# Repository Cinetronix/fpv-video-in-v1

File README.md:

# Cinetronix FPV Video Input Board v1

KiCad hardware design for an HDMI-to-MIPI CSI bridge board, designed for FPV camera systems.

## Overview

Converts HDMI video input to MIPI CSI-2 output using the Toshiba TC9590XBG bridge IC, controlled by an ESP32-S3 microcontroller.

### Key Components

| Component | Function |
|-----------|----------|
| TC9590XBG | HDMI to MIPI CSI-2 bridge |
| ESP32-S3 | Control MCU |
| TS5MP645YFPR | HDMI multiplexer |
| TPD8S009DSMR | HDMI ESD protection |
| TPD6E05U06RVZR | Additional ESD protection |
| DF56C-26S | Micro-coax connector (CSI output) |

## Board Designs

- **TC9590XBG-PCB/** — Main board with HDMI input, CSI output, and ESP32-S3 control
- **DF56C-26S-breakout-board-PCB/** — Breakout board for the 26-pin DF56C micro-coax connector
- **DF56C-30S-breakout-board-PCB/** — Breakout board for the 30-pin DF56C micro-coax connector

## Requirements

- [KiCad](https://www.kicad.org/) 7+
- [KiKit](https://github.com/yaqwsx/KiKit) (for panel generation)

## Panelization

Generate a manufacturing panel from the `TC9590XBG-PCB/` directory:

```bash
kikit panelize \
    --layout "grid; rows: 1; cols: 3; space: 5mm;" \
    --tabs "fixed; width: 5mm;" \
    --cuts "mousebites; drill: 0.5mm; spacing: 1mm; offset: 0.2mm; prolong: 0.5mm" \
    --framing "railstb; width: 5mm; space: 3mm; mintotalheight: 72mm; mintotalwidth: 72mm" \
    --tooling "3hole; hoffset: 2.5mm; voffset: 2.5mm; size: 1.5mm" \
    --fiducials "3fid; hoffset: 5mm; voffset: 2.5mm; coppersize: 2mm; opening: 1mm;" \
    --text "simple; text: Cinetronix Video input v1.1a; anchor: mt; voffset: 2.5mm; hjustify: center; vjustify: center;" \
    --post "millradius: 1mm" \
    fpv-video-in-v1.kicad_pcb Panel/panel.kicad_pcb
```

## Project Structure

Each board subdirectory contains its own KiCad project files (`.kicad_pro`, `.kicad_sch`, `.kicad_pcb`) along with a `lib/` directory for custom symbols, footprints, and 3D models.

## License

Copyright Cinetronix. All rights reserved.

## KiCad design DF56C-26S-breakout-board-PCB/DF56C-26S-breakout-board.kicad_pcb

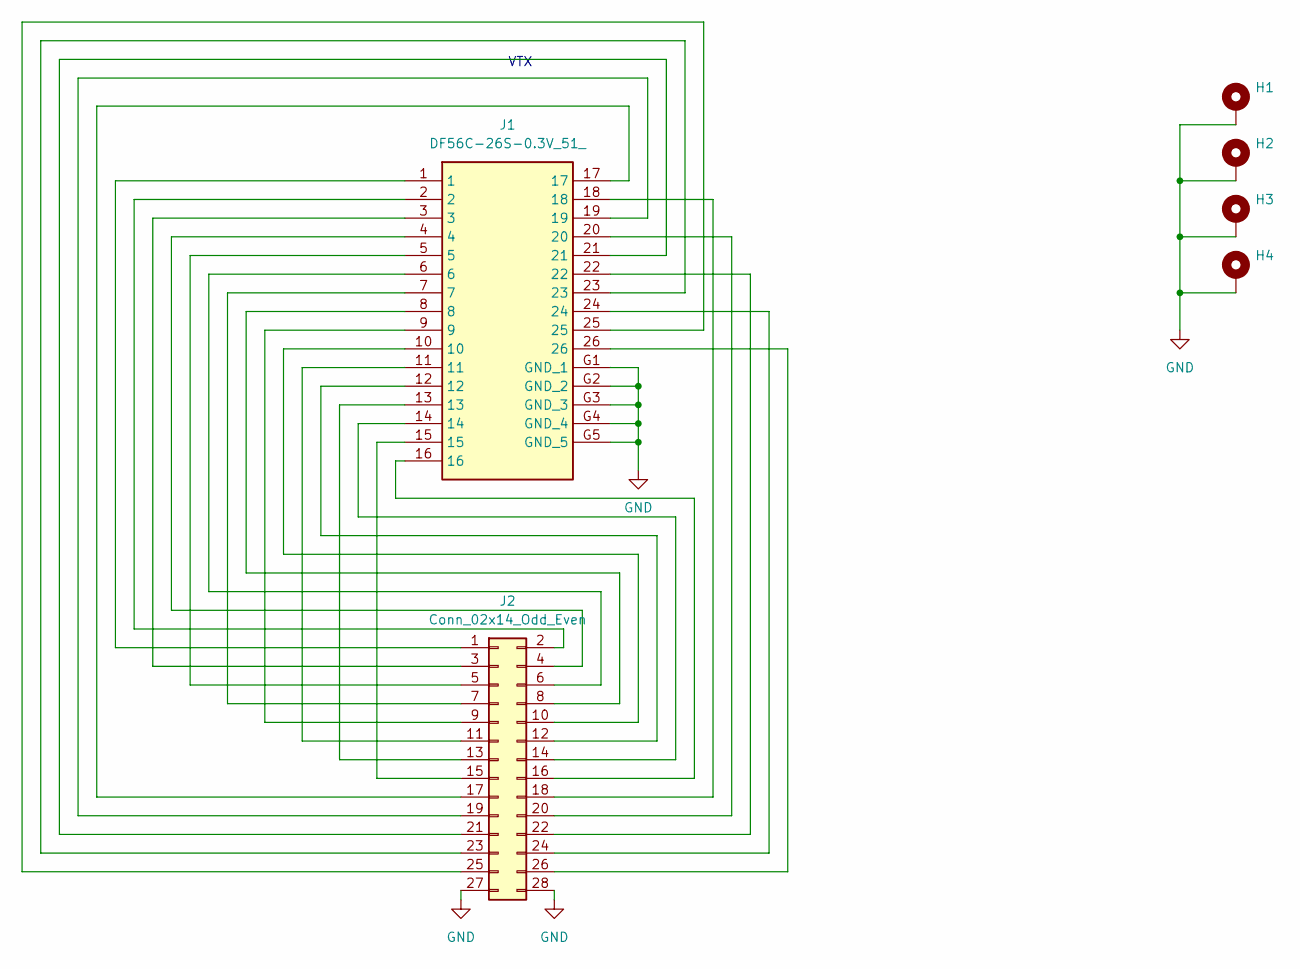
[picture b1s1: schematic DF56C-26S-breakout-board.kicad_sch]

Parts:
H1, H2, H3, H4: MountingHole_Pad; MountingHole_2.2mm_M2_Pad_Via
J1: DF56C-26S-0.3V_51_; DF56C26S03V51; Mouser Part Number 798-DF56C-26S-0.3V51
J2: Conn_02x14_Odd_Even; PinHeader_2x14_P2.54mm_Vertical

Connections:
GND: H1.1, H2.1, H3.1, H4.1, J1.G1 (GND_1), J1.G2 (GND_2), J1.G3 (GND_3), J1.G4 (GND_4), J1.G5 (GND_5), J2.27, J2.28
unnamed: J1.1, J2.1
unnamed: J1.2, J2.2
unnamed: J1.3, J2.3
unnamed: J1.4, J2.4
unnamed: J1.5, J2.5
unnamed: J1.6, J2.6
unnamed: J1.7, J2.7
unnamed: J1.8, J2.8
unnamed: J1.9, J2.9
unnamed: J1.10, J2.10
unnamed: J1.11, J2.11
unnamed: J1.12, J2.12
unnamed: J1.13, J2.13
unnamed: J1.14, J2.14
unnamed: J1.15, J2.15
unnamed: J1.16, J2.16
unnamed: J1.17, J2.17
unnamed: J1.18, J2.18
unnamed: J1.19, J2.19
unnamed: J1.20, J2.20
unnamed: J1.21, J2.21
unnamed: J1.22, J2.22
unnamed: J1.23, J2.23
unnamed: J1.24, J2.24
unnamed: J1.25, J2.25
unnamed: J1.26, J2.26

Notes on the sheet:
VTX

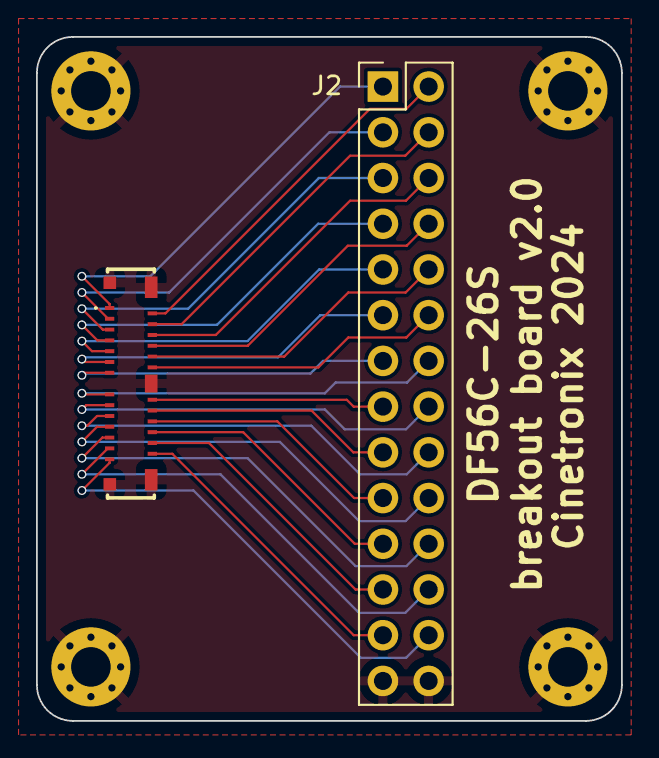
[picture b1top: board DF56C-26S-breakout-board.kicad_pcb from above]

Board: 2 copper layers, 32.5 x 38.0 mm, 6 parts (0 on the bottom side), 27 nets.

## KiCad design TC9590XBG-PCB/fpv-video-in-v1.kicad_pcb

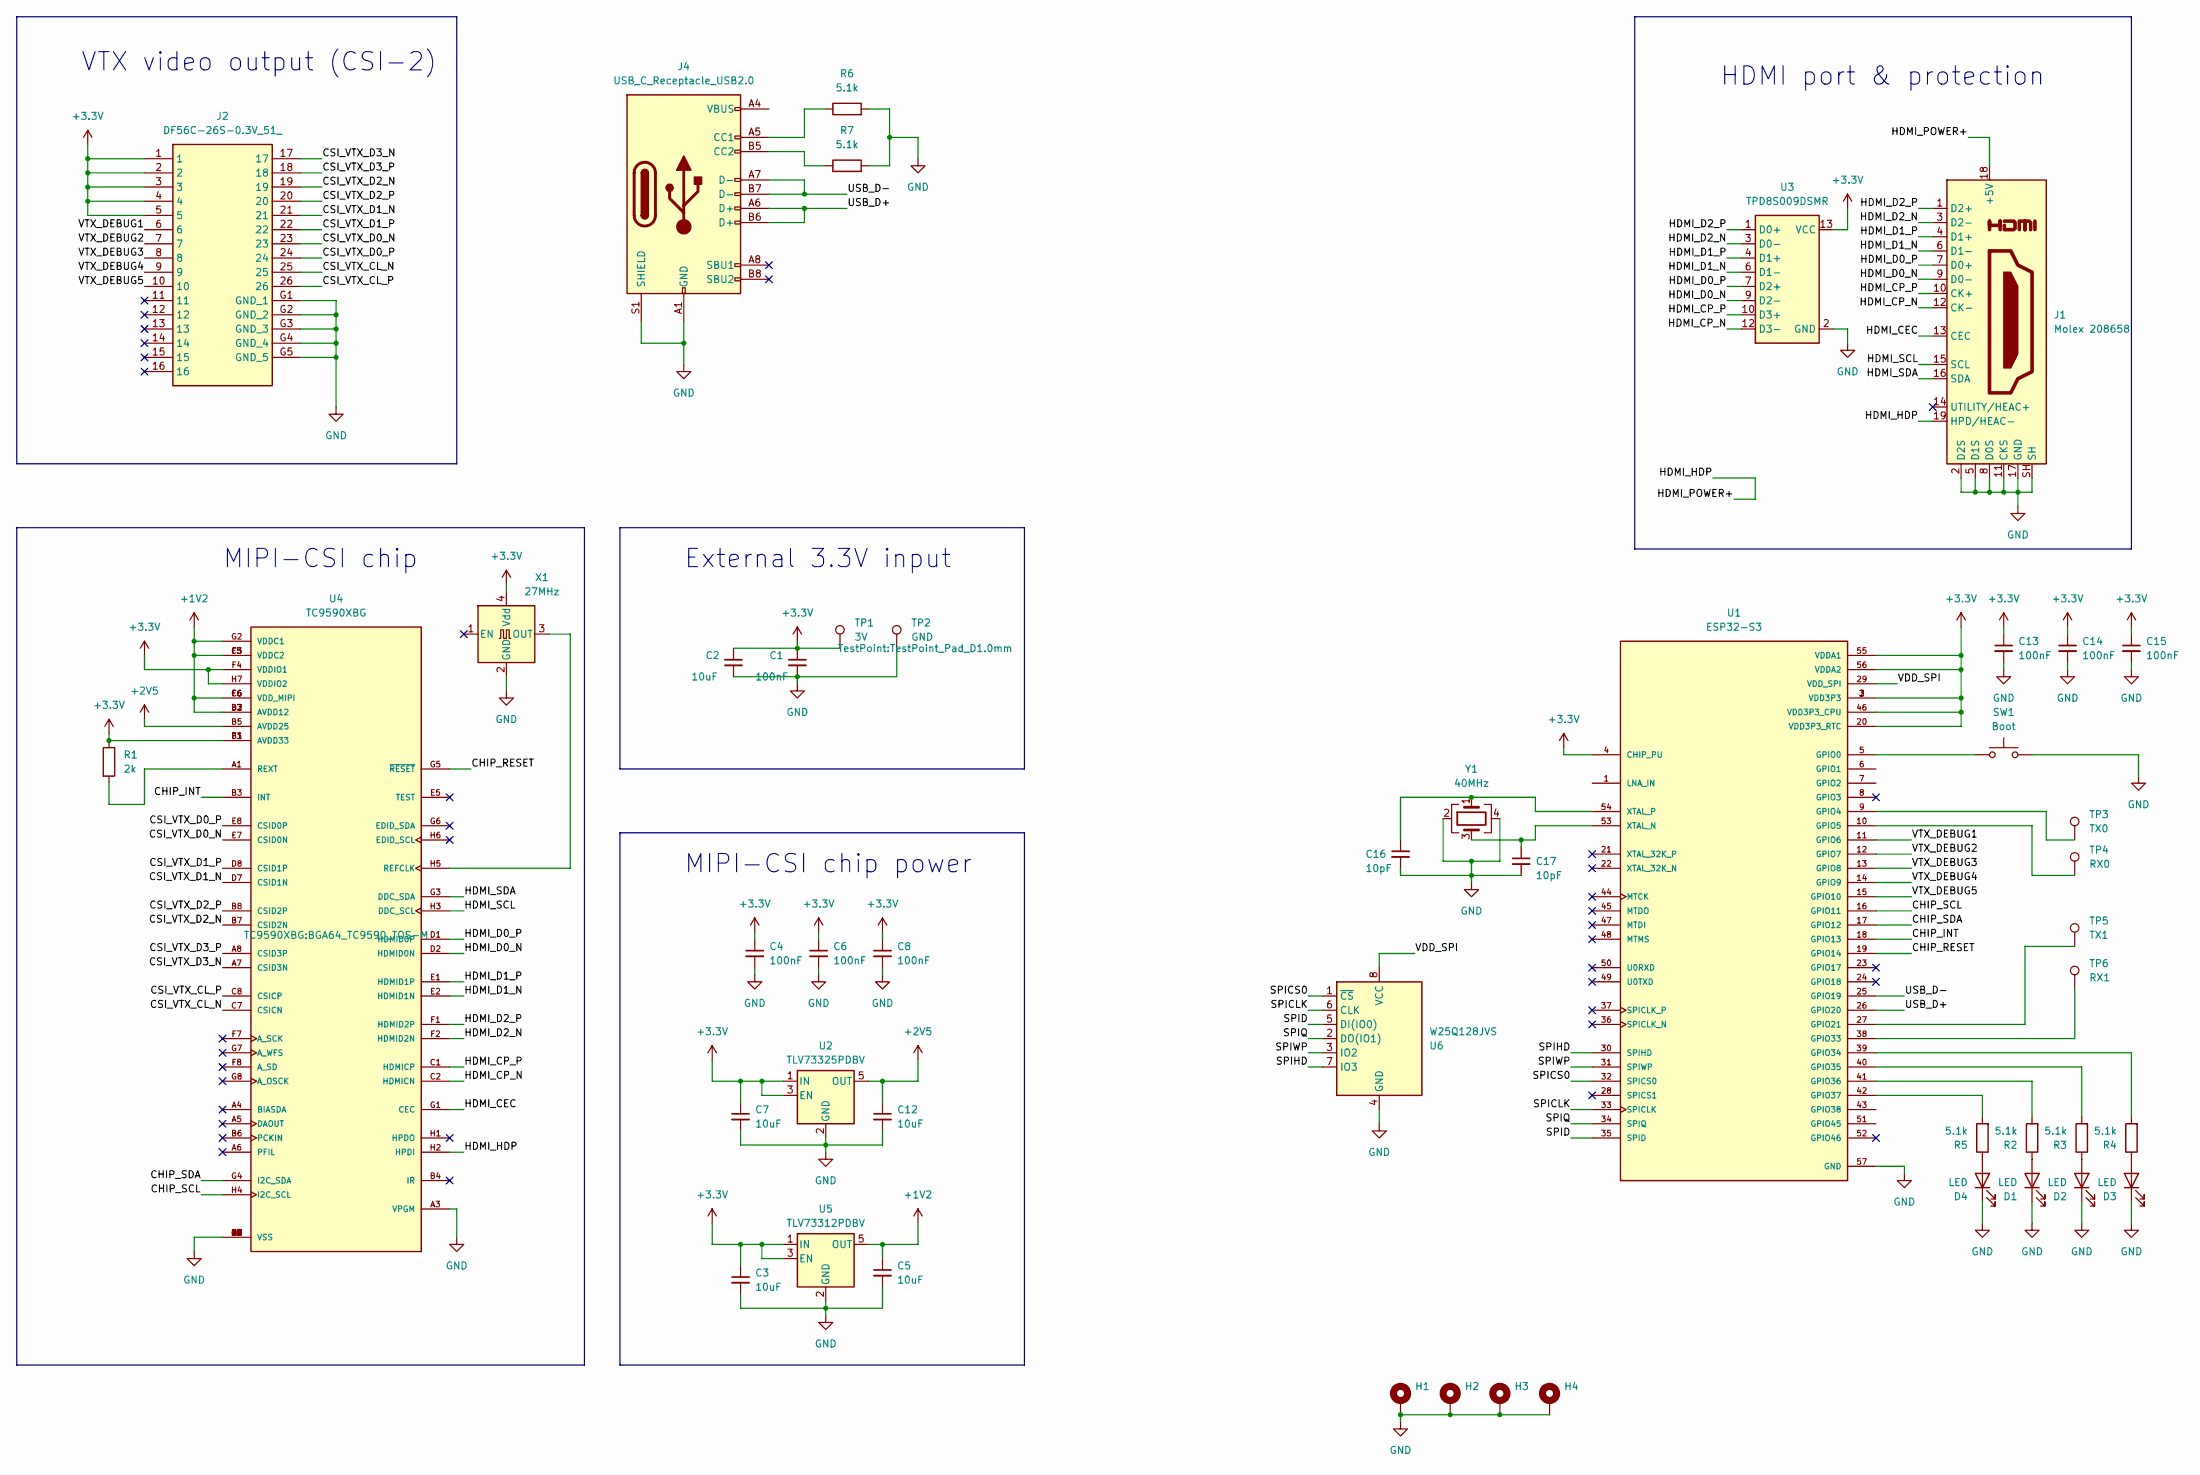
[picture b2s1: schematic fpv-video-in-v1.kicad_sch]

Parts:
C1, C4, C6, C8, C13, C14, C15: 100nF; C_0402_1005Metric
C2, C3, C5, C7, C12: 10uF; C_0402_1005Metric
C16, C17: 10pF; C_0402_1005Metric
D1, D2, D3, D4: LED; LED_0603_1608Metric
H1, H2, H3, H4: MountingHole_Pad; MountingHole_2.2mm_M2_Pad
J1: Molex 208658; HDMI_A_Molex_208658-1001_Horizontal
J2: DF56C-26S-0.3V_51_; DF56C26S03V51; Mouser Part Number 798-DF56C-26S-0.3V51
J4: USB_C_Receptacle_USB2.0; USB_C_Receptacle_G-Switch_GT-USB-7010ASV
R1: 2k; R_0402_1005Metric
R2, R3, R4, R5, R6, R7: 5.1k; R_0402_1005Metric
SW1: Boot; SW_Push_SPST_NO_Alps_SKRK; LCSC C115357
TP1: 3V; TestPoint_Pad_D1.0mm
TP2: GND; TestPoint_Pad_D1.0mm
TP3: TX0; TestPoint_Pad_D1.5mm
TP4: RX0; TestPoint_Pad_D1.5mm
TP5: TX1; TestPoint_Pad_D1.0mm
TP6: RX1; TestPoint_Pad_D1.0mm
U1: ESP32-S3; QFN40P700X700X90-57N-D; PARTREV v1.2
U2: TLV73325PDBV; SOT-23-5
U3: TPD8S009DSMR; R-PDSO-N15; MPN TPD8S009DSMR
U4: TC9590XBG; BGA64_TC9590_TOS-M; PARTREV 1.4
U5: TLV73312PDBV; SOT-23-5
U6: W25Q128JVS; WSON-8-1EP_6x5mm_P1.27mm_EP3.4x4.3mm
X1: 27MHz; Crystal_SMD_2016-4Pin_2.0x1.6mm
Y1: 40MHz; Crystal_SMD_2016-4Pin_2.0x1.6mm

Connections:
+1V2: C5.1, U4.B2 (AVDD12), U4.C3 (VDDC2), U4.C6 (VDD_MIPI), U4.D3 (AVDD12), U4.F5 (VDDC2), U4.F6 (VDD_MIPI), U4.G2 (VDDC1), U5.5 (OUT)
+2V5: C12.1, U2.5 (OUT), U4.B5 (AVDD25)
+3.3V: C1.1, C2.1, C3.1, C4.1, C6.1, C7.1, C8.1, C13.1, C14.1, C15.1, J2.1, J2.2, J2.3, J2.4, J2.5, R1.1, TP1.1, U1.2 (VDD3P3), U1.3 (VDD3P3), U1.4 (CHIP_PU), U1.20 (VDD3P3_RTC), U1.46 (VDD3P3_CPU), U1.55 (VDDA1), U1.56 (VDDA2), U2.1 (IN), U2.3 (EN), U3.13 (VCC), U3.15 (VCC), U4.B1 (AVDD33), U4.F3 (AVDD33), U4.F4 (VDDIO1), U4.H7 (VDDIO2), U5.1 (IN), U5.3 (EN), X1.4 (Vdd)
/CHIP_INT: U1.18 (GPIO13), U4.B3 (INT)
/CHIP_RESET: U1.19 (GPIO14), U4.G5 (~RESET)
/CHIP_SCL: U1.16 (GPIO11), U4.H4 (I2C_SCL)
/CHIP_SDA: U1.17 (GPIO12), U4.G4 (I2C_SDA)
/CSI_VTX_CL_N: J2.25, U4.C7 (CSICN)
/CSI_VTX_CL_P: J2.26, U4.C8 (CSICP)
/CSI_VTX_D0_N: J2.23, U4.E7 (CSID0N)
/CSI_VTX_D0_P: J2.24, U4.E8 (CSID0P)
/CSI_VTX_D1_N: J2.21, U4.D7 (CSID1N)
/CSI_VTX_D1_P: J2.22, U4.D8 (CSID1P)
/CSI_VTX_D2_N: J2.19, U4.B7 (CSID2N)
/CSI_VTX_D2_P: J2.20, U4.B8 (CSID2P)
/CSI_VTX_D3_N: J2.17, U4.A7 (CSID3N)
/CSI_VTX_D3_P: J2.18, U4.A8 (CSID3P)
/HDMI_CEC: J1.13 (CEC), U4.G1 (CEC)
/HDMI_CP_N: J1.12 (CK-), U3.12 (D3-), U4.C2 (HDMICN)
/HDMI_CP_P: J1.10 (CK+), U3.10 (D3+), U4.C1 (HDMICP)
/HDMI_D0_N: J1.9 (D0-), U3.9 (D2-), U4.D2 (HDMID0N)
/HDMI_D0_P: J1.7 (D0+), U3.7 (D2+), U4.D1 (HDMID0P)
/HDMI_D1_N: J1.6 (D1-), U3.6 (D1-), U4.E2 (HDMID1N)
/HDMI_D1_P: J1.4 (D1+), U3.4 (D1+), U4.E1 (HDMID1P)
/HDMI_D2_N: J1.3 (D2-), U3.3 (D0-), U4.F2 (HDMID2N)
/HDMI_D2_P: J1.1 (D2+), U3.1 (D0+), U4.F1 (HDMID2P)
/HDMI_HDP: J1.18 (+5V), J1.19 (HPD/HEAC-), U4.H2 (HPDI)
/HDMI_SCL: J1.15 (SCL), U4.H3 (DDC_SCL)
/HDMI_SDA: J1.16 (SDA), U4.G3 (DDC_SDA)
/SPICLK: U1.33 (SPICLK), U6.6 (CLK)
/SPICS0: U1.32 (SPICS0), U6.1 (~CS)
/SPID: U1.35 (SPID), U6.5 (DI(IO0))
/SPIHD: U1.30 (SPIHD), U6.7 (IO3)
/SPIQ: U1.34 (SPIQ), U6.2 (DO(IO1))
/SPIWP: U1.31 (SPIWP), U6.3 (IO2)
/USB_D+: J4.A6 (D+), J4.B6 (D+), U1.26 (GPIO20)
/USB_D-: J4.A7 (D-), J4.B7 (D-), U1.25 (GPIO19)
/VDD_SPI: U1.29 (VDD_SPI), U6.8 (VCC)
/VTX_DEBUG1: J2.6, U1.11 (GPIO6)
/VTX_DEBUG2: J2.7, U1.12 (GPIO7)
/VTX_DEBUG3: J2.8, U1.13 (GPIO8)
/VTX_DEBUG4: J2.9, U1.14 (GPIO9)
/VTX_DEBUG5: J2.10, U1.15 (GPIO10)
GND: C1.2, C2.2, C3.2, C4.2, C5.2, C6.2, C7.2, C8.2, C12.2, C13.2, C14.2, C15.2, C16.2, C17.2, D1.1 (K), D2.1 (K), D3.1 (K), D4.1 (K), H1.1, H2.1, H3.1, H4.1, J1.2 (D2S), J1.5 (D1S), J1.8 (D0S), J1.11 (CKS), J1.17 (GND), J1.SH, J2.G1 (GND_1), J2.G2 (GND_2), J2.G3 (GND_3), J2.G4 (GND_4), J2.G5 (GND_5), J4.A1 (GND), J4.A12 (GND), J4.B1 (GND), J4.B12 (GND), J4.S1 (SHIELD), R6.2, R7.2, SW1.2, TP2.1, U1.57 (GND), U2.2 (GND), U3.2 (GND), U3.5 (GND), U3.8 (GND), U3.11 (GND), U4.A2 (VSS), U4.A3 (VPGM), U4.C4 (VSS), U4.C5 (VSS), U4.D4 (VSS), U4.D5 (VSS), U4.D6 (VSS), U4.E3 (VSS), U4.E4 (VSS), U4.E6 (VSS), U4.H8 (VSS), U5.2 (GND), U6.4 (GND), X1.2 (GND), Y1.2, Y1.4
unnamed: D1.2 (A), R2.1
unnamed: D2.2 (A), R3.1
unnamed: D3.2 (A), R4.1
unnamed: D4.2 (A), R5.1
unnamed: J4.A5 (CC1), R6.1
unnamed: J4.B5 (CC2), R7.1
unnamed: J4.A4 (VBUS), J4.A9 (VBUS), J4.B4 (VBUS), J4.B9 (VBUS)
unnamed: SW1.1, U1.5 (GPIO0)
unnamed: TP3.1, U1.9 (GPIO4)
unnamed: TP4.1, U1.10 (GPIO5)
unnamed: TP5.1, U1.27 (GPIO21)
unnamed: TP6.1, U1.38 (GPIO33)
unnamed: R4.2, U1.39 (GPIO34)
unnamed: R3.2, U1.40 (GPIO35)
unnamed: R2.2, U1.41 (GPIO36)
unnamed: R5.2, U1.42 (GPIO37)
unnamed: C17.1, U1.53 (XTAL_N), Y1.3
unnamed: C16.1, U1.54 (XTAL_P), Y1.1
unnamed: U4.H5 (REFCLK), X1.3 (OUT)
unnamed: R1.2, U4.A1 (REXT)

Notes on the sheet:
HDMI port & protection
MIPI-CSI chip power
MIPI-CSI chip
VTX video output (CSI-2)
External 3.3V input

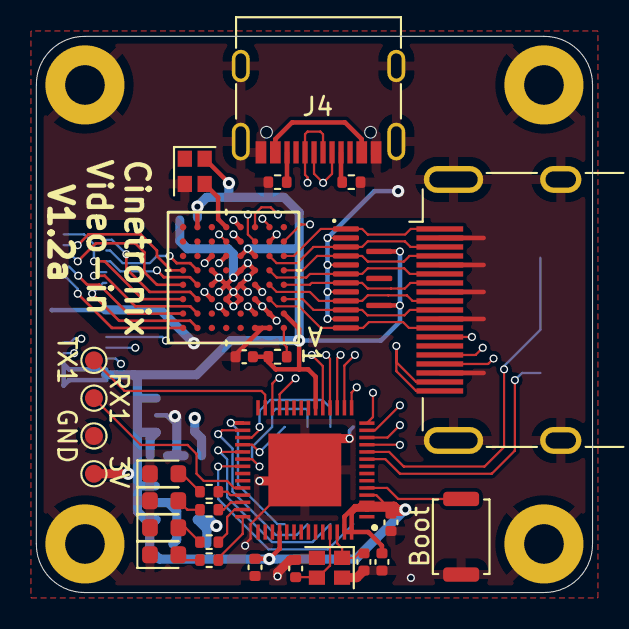
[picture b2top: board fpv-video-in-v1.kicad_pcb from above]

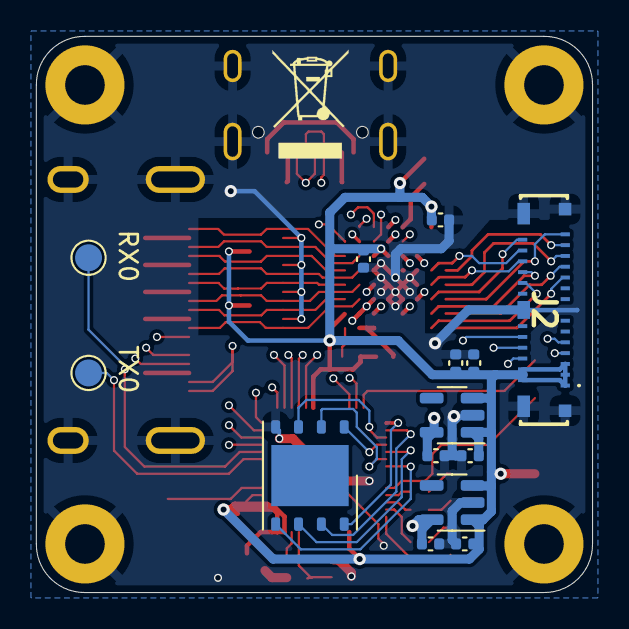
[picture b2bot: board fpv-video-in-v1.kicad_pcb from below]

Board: 4 copper layers, 30.9 x 30.9 mm, 47 parts (14 on the bottom side), 64 nets.

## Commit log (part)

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2024-08-06 Add DF56C-30S dev board
2024-08-06 Add DF56C-26S dev board
2024-08-06 Update gitignore
2024-08-06 Add TC9590 implementation
2024-08-06 Rename boards
2026-04-03 Add github action, CLAUDE.md and README.md
2026-04-03 Split schematic PDF export into its own step
    The schematic PDF wasn't being generated when combined with run_erc
    in the same action invocation.
2026-04-03 Bump actions-for-kicad/kicad-actions from 1.6.pre.k9.0 to 9.0.4
    Bumps [actions-for-kicad/kicad-actions](https://github.com/actions-for-kicad/kicad-actions) from 1.6.pre.k9.0 to 9.0.4.
    - [Release notes](https://github.com/actions-for-kicad/kicad-actions/releases)
    - [Changelog](https://github.com/actions-for-kicad/kicad-actions/blob/main/release-procdure.md)
    - [Commits](https://github.com/actions-for-kicad/kicad-actions/compare/v1.6-k9.0...v1.6-k9.0.4)
    ---
    updated-dependencies:
2026-04-03 Bump actions/upload-artifact from 4 to 7
    Bumps [actions/upload-artifact](https://github.com/actions/upload-artifact) from 4 to 7.
    - [Release notes](https://github.com/actions/upload-artifact/releases)
    - [Commits](https://github.com/actions/upload-artifact/compare/v4...v7)
    ---
    updated-dependencies:
    - dependency-name: actions/upload-artifact
2026-04-03 Bump actions/checkout from 4 to 6
    Bumps [actions/checkout](https://github.com/actions/checkout) from 4 to 6.
    - [Release notes](https://github.com/actions/checkout/releases)
    - [Changelog](https://github.com/actions/checkout/blob/main/CHANGELOG.md)
    - [Commits](https://github.com/actions/checkout/compare/v4...v6)
    ---
    updated-dependencies:
2026-06-19 Bump actions/checkout from 6 to 7
    Bumps [actions/checkout](https://github.com/actions/checkout) from 6 to 7.
    - [Release notes](https://github.com/actions/checkout/releases)
    - [Changelog](https://github.com/actions/checkout/blob/main/CHANGELOG.md)
    - [Commits](https://github.com/actions/checkout/compare/v6...v7)
    ---
    updated-dependencies:

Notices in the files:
parts and their libraries:
License: Apache-2.0
